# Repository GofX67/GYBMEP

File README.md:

# GYBMEP

Eagle Library for chinese GYBMEP / BME280 & WEMOS D1 Mini Shield

Bought this one from Aliexpress:<br>
<a href="https://de.aliexpress.com/item/BME280-Digital-Sensor-Temperature-Humidity-Barometric-Pressure-Sensor-New/32665342978.html?spm=a2g0s.9042311.0.0.ohOeMC">https://de.aliexpress.com/item/BME280-Digital-Sensor-Temperature-Humidity-Barometric-Pressure-Sensor-New/32665342978.html?spm=a2g0s.9042311.0.0.ohOeMC</a>

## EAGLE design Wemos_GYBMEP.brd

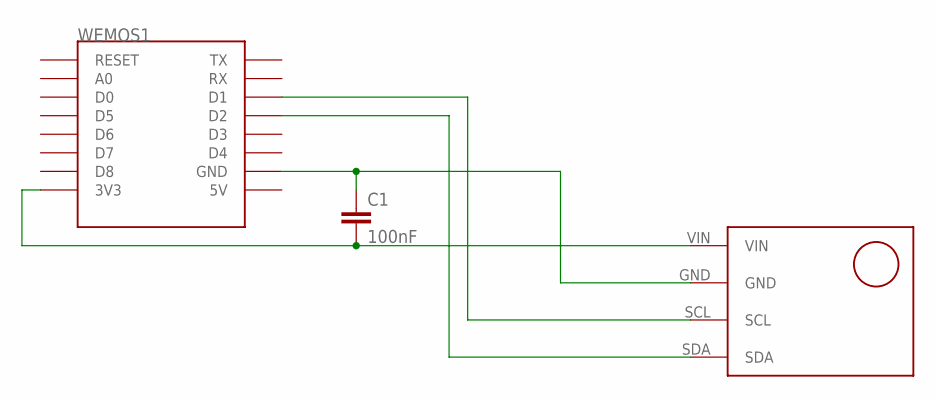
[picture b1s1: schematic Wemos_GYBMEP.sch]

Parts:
C1: 100nF; C5B2.5
U$1: GYBMEP
WEMOS1: WEMOS-D1-MINI

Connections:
unnamed: C1.2, U$1.VIN, WEMOS1.3V3
unnamed: C1.1, U$1.GND, WEMOS1.GND
unnamed: U$1.SCL, WEMOS1.D1
unnamed: U$1.SDA, WEMOS1.D2

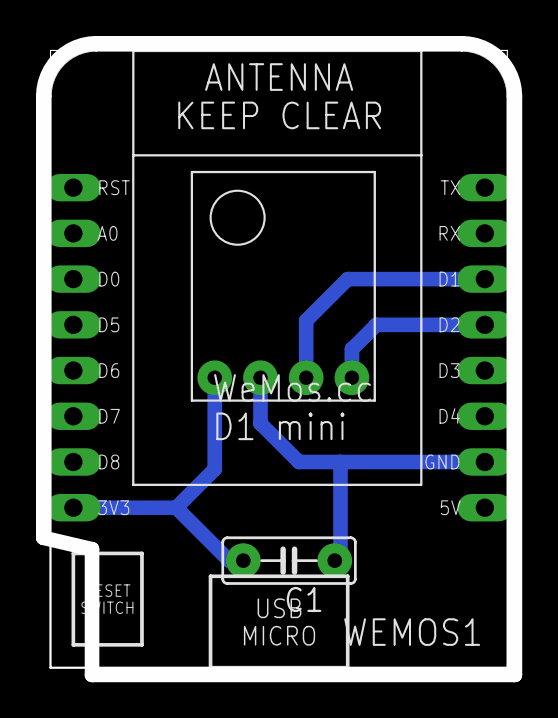
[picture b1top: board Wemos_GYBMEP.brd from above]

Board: 2 copper layers, 26.2 x 35.1 mm, 3 parts (0 on the bottom side), 4 nets.

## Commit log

2018-03-04 Create LICENSE
